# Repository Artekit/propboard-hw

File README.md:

# Artekit PropBoard Hardware

This repository contains hardware-related files for the [Artekit PropBoard](https://www.artekit.eu/products/devboards/propboard/).

## Documentation

* [Product page](https://www.artekit.eu/products/devboards/propboard/)
* [Manual & APIs](https://www.artekit.eu/doc/categories/propboard/)

## License

Released under the Creative Commons Attribution Share-Alike 3.0 License (http://creativecommons.org/licenses/by-sa/3.0)

Copyright (c) 2017 Artekit Labs.

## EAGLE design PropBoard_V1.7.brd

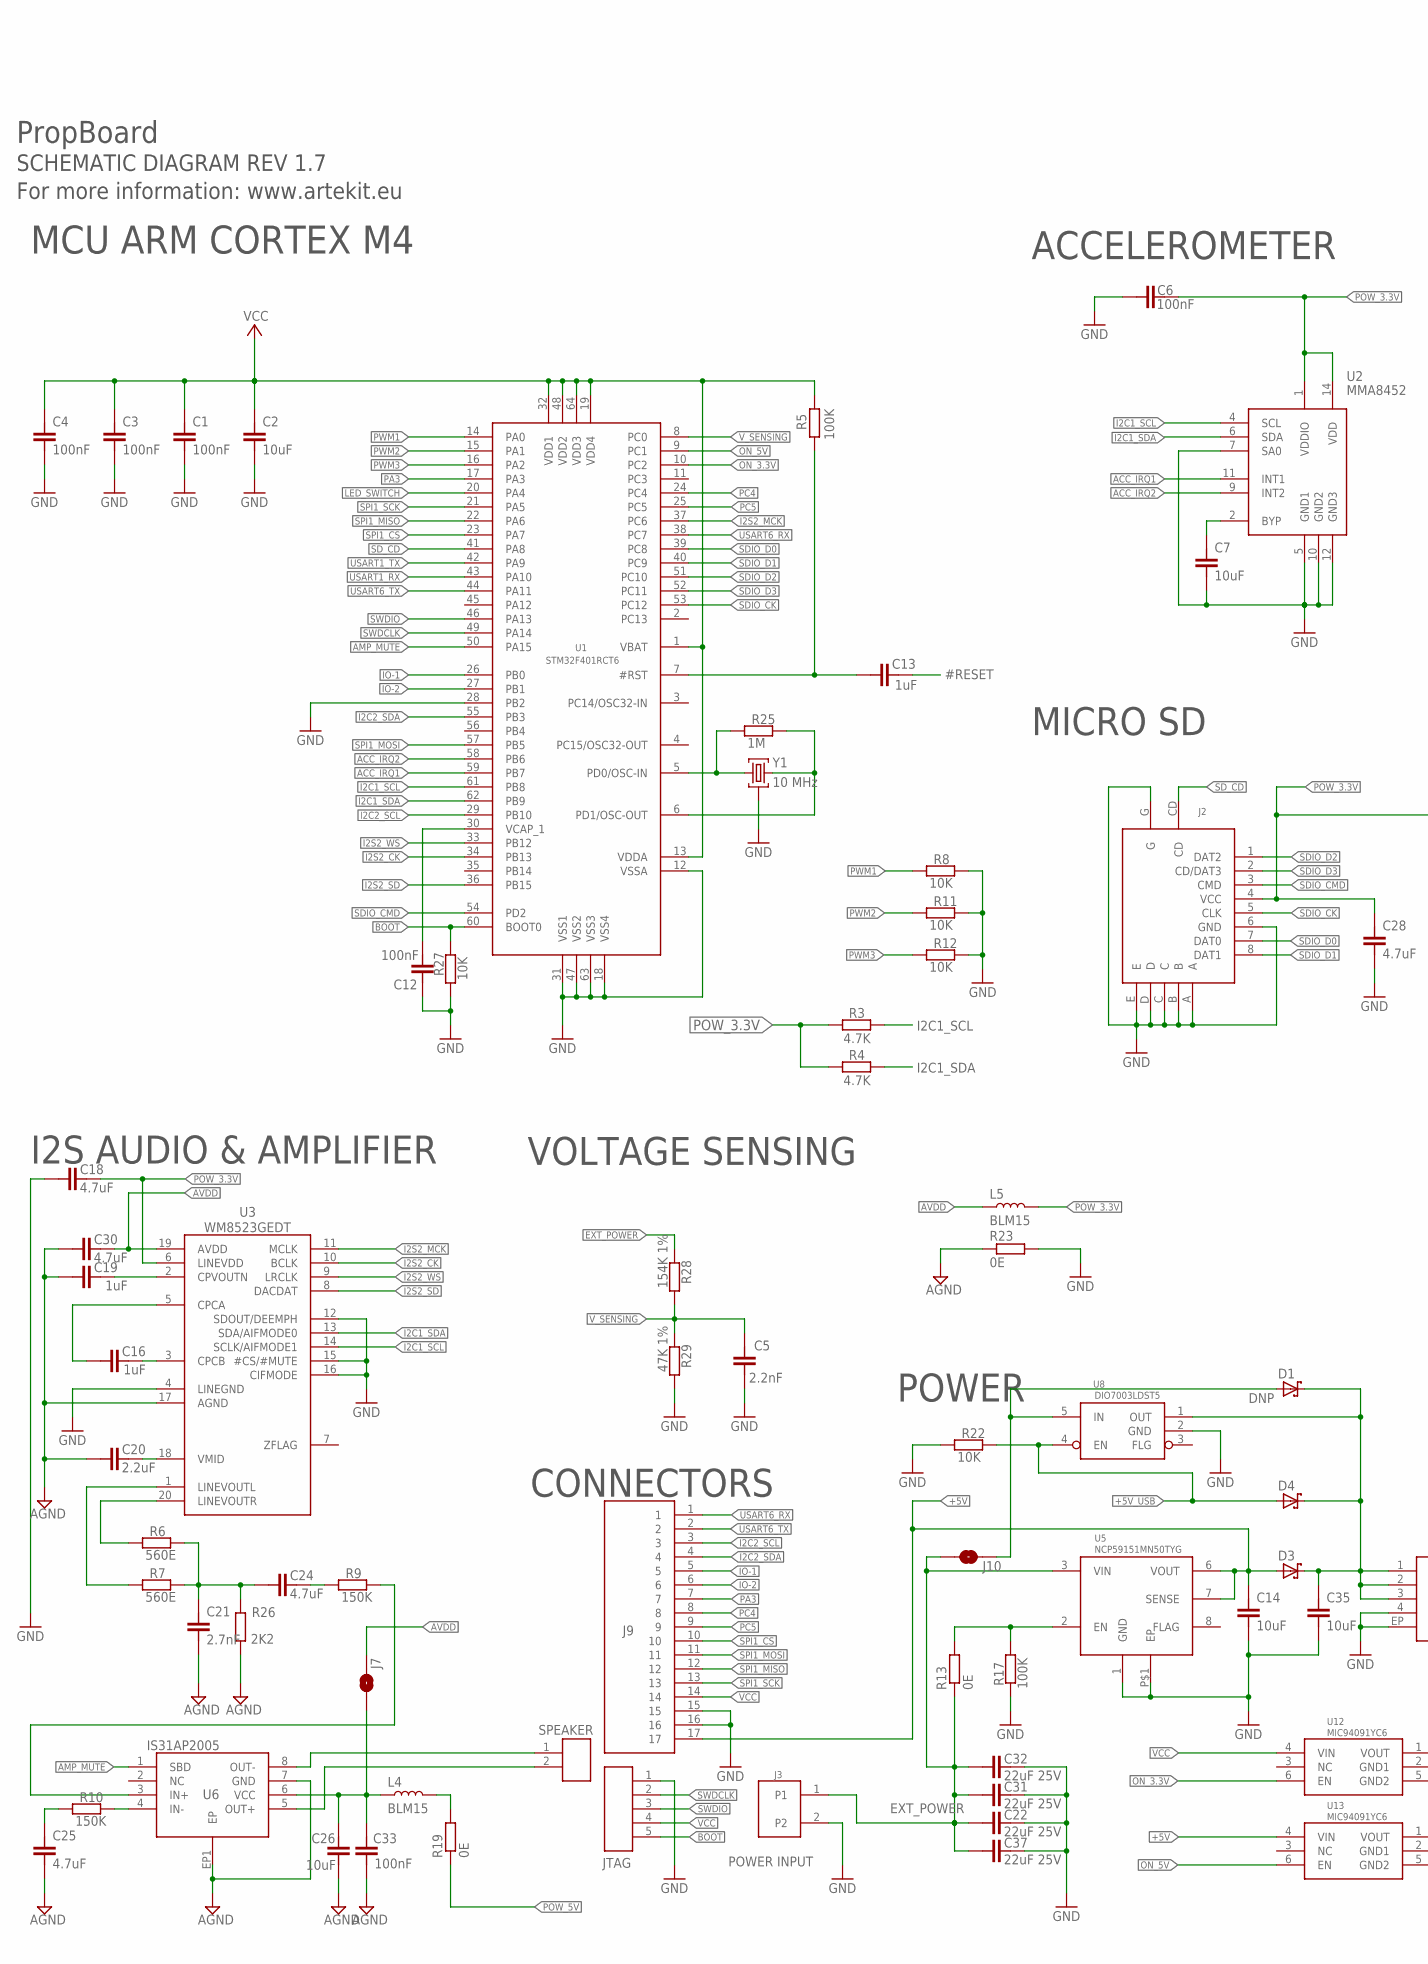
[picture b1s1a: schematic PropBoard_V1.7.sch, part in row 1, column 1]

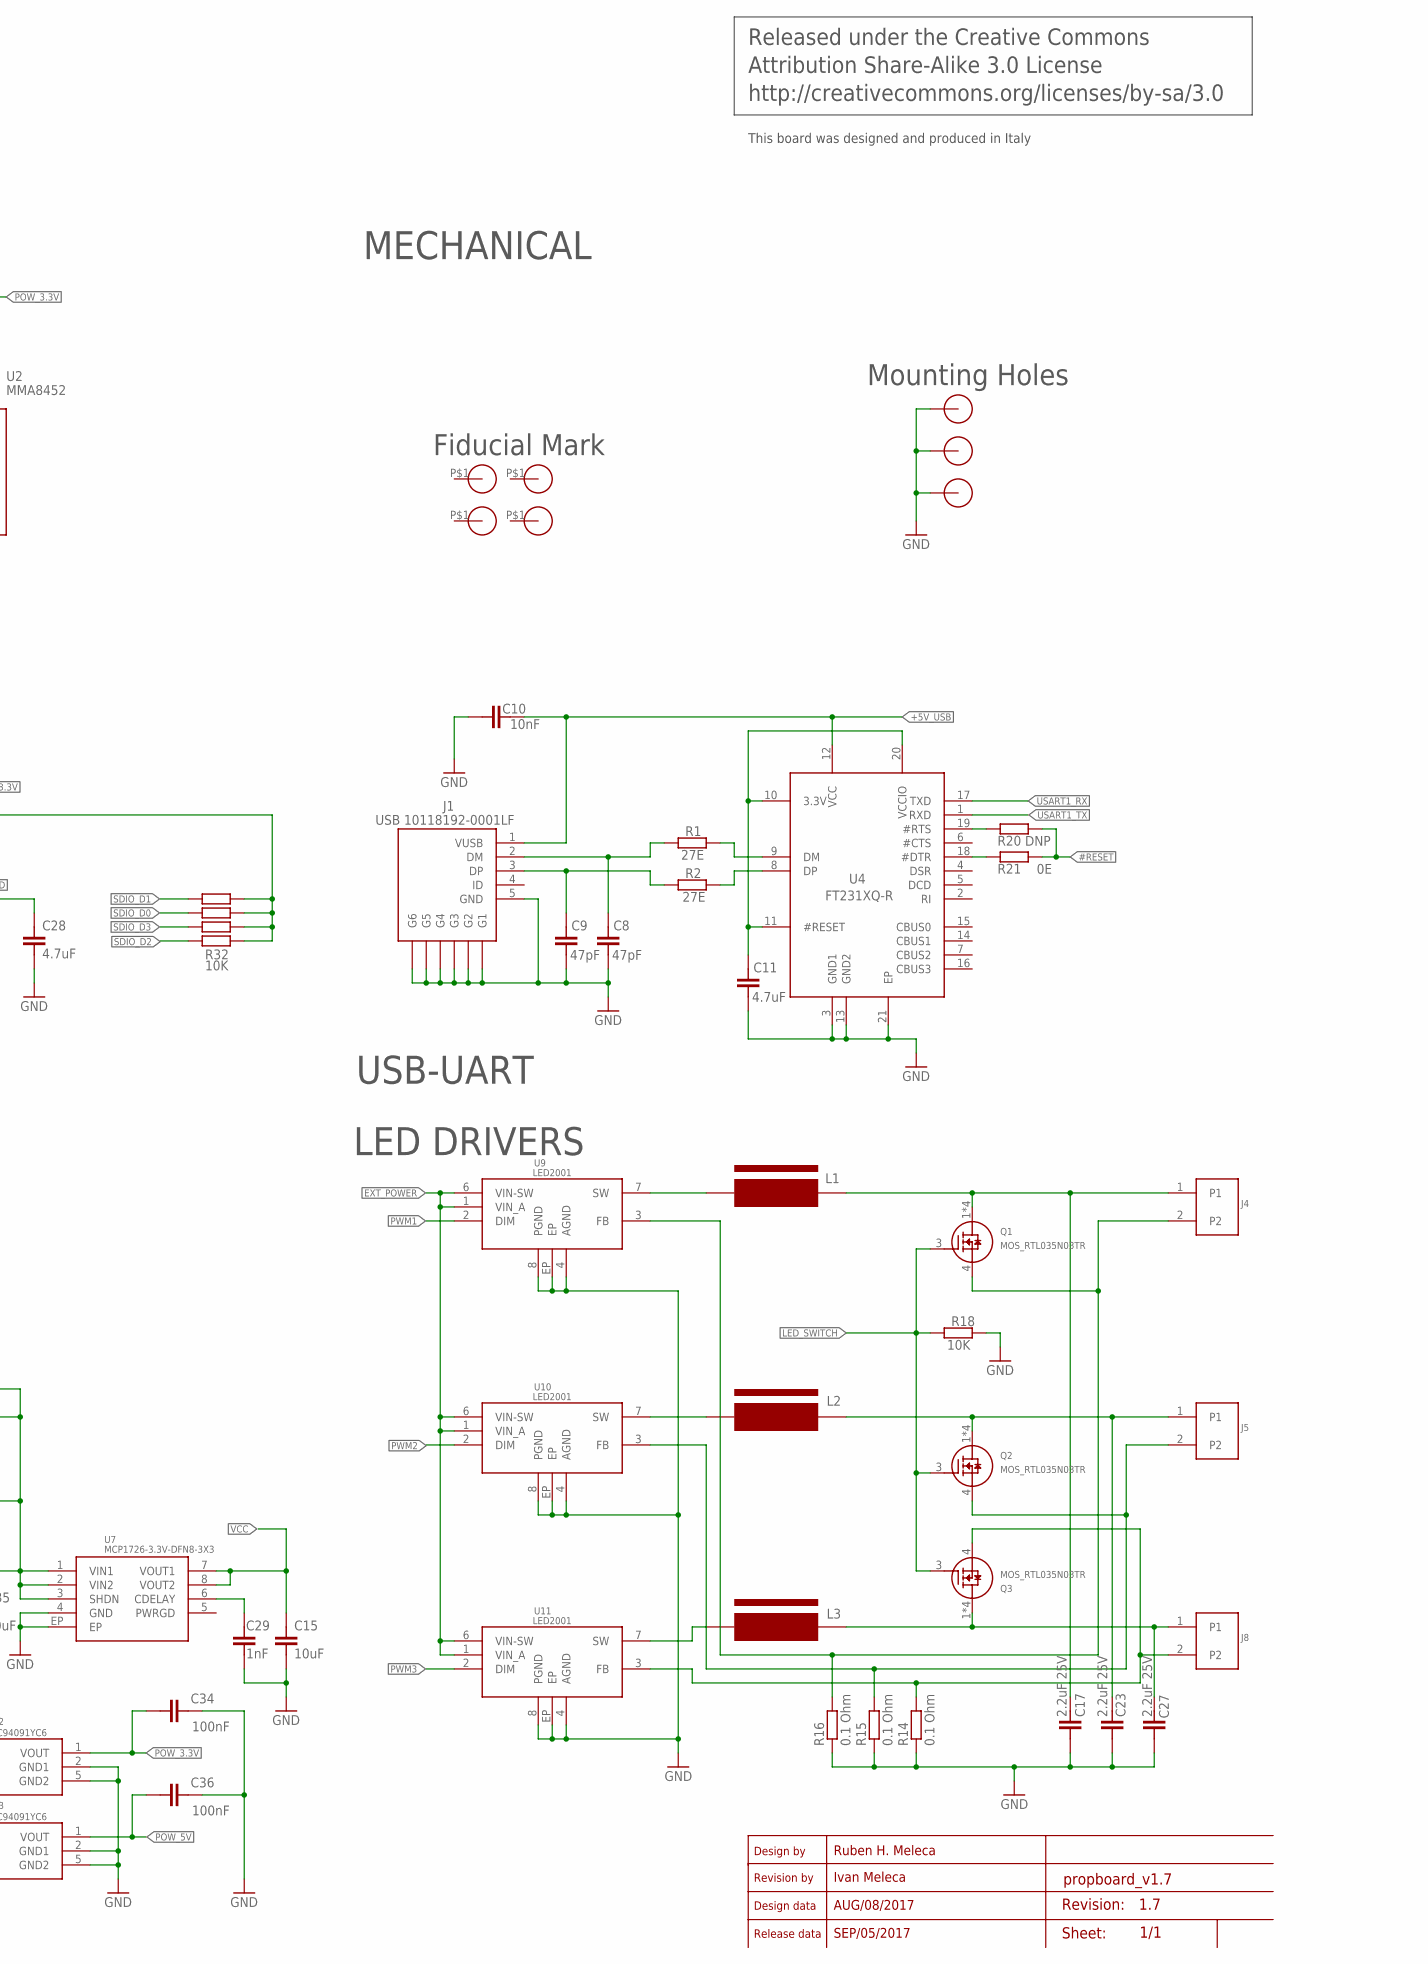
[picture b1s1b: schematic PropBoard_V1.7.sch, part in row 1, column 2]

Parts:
C1, C3, C4, C6, C12, C33, C34, C36: 100nF; C0402
C2, C7, C14, C15, C26, C35: 10uF; C0402
C5: 2.2nF; C0402
C8, C9: 47pF; C0402
C10: 10nF; C0402
C11, C18, C24, C25, C28, C30: 4.7uF; C0402
C13, C19: 1uF; C0402
C16: 1uF; C0402-WIDE
C17, C23, C27: 2.2uF 25V; C0603
C20: 2.2uF; C0402
C21: 2.7nF; C0402
C22, C31, C32, C37: 22uF 25V; C0805
C29: 1nF; C0402
D1: DNP; SOD-323
D3, D4: BAT60; SOD-323
J1: USB 10118192-0001LF; CON-USB-MICRO-B-SMD
J2: MICRO-SD-CON-MOLEX-503182-0852
J3: PROP-POWER-PAD; 2-WAY-POWER-PAD
J4, J5, J8: PROP-LED-PAD; 2-WAY-POWER-PAD-SMALL
J6: CON-PH-1X02-P0.1"2MM; PIN-HEADER-1X02-P2MM
J7, J10: JUMPER-1-OPEN
J9: CON-PH-1X17-P0.1; PIN-HEADER-1X17-NODASH
L1, L2, L3: SRN6028-3R9M; IND-MURATA-DG6050-SERIES; MPN SRN6028-3R9M
L4, L5: BLM15; I0402; MPN BLM15AG102SN1
Q1, Q2, Q3: MOS_RTL035N03TR; SOT-363-6
R1, R2: 27E; R0402
R3, R4: 4.7K; R0402
R5, R17: 100K; R0402
R6, R7: 560E; R0402
R8, R11, R12, R18, R22, R27: 10K; R0402
R9, R10: 150K; R0402
R13, R19: 0E; R0603
R14, R15, R16: 0.1 Ohm; R0805
R20: DNP; R0402
R21: 0E; R0402
R23: 0E; R0402; MPN BLM15AG102SN1
R25: 1M; R0402
R26: 2K2; R0402
R28: 154K 1%; R0402
R29: 47K 1%; R0402
R32: 10K; RES-ARRAY-0603
U1: STM32F401RCT6; LQFP64-10X10-P0.50; MPN STM32F401RCT6
U2: MMA8452; QFN-COL-16-3X3-P0.50-MMA8452
U3: WM8523GEDT; TSSOP-20
U4: FT231XQ-R; QFN20-4X4-P0.50
U5: NCP59151MN50TYG; DFN8-4X4
U6: IS31AP2005; DFN-8-3X3MM-P0.65
U7: MCP1726-3.3V-DFN8-3X3; DFN8-3X3
U8: DIO7003LDST5; SOT23-5
U9, U10, U11: LED2001; VFQFPN-8
U12, U13: MIC94091YC6; SOT363-6
U$1: CON-PH-1X05-P0.1"; PIN-HEADER-1X05-NODASH
U$2, U$3, U$4: HOLE-2MM-METALIZED
U$5, U$6, U$8, U$9: FIDUTIAL_1.2MM
Y1: 10 MHz; RESONATOR-MURATA-CSTCE-SERIES

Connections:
#RESET: C13.2, R20.1, R21.1
+5V: C14.1, D3.A, J9.17, U5.6 (VOUT), U5.7 (SENSE), U13.4 (VIN)
+5V_USB: C10.2, D4.A, J1.1 (VUSB), R22.2, U4.12 (VCC), U8.4 (EN)
ACC_IRQ1: U1.59 (PB7), U2.11 (INT1)
ACC_IRQ2: U1.58 (PB6), U2.9 (INT2)
AGND: C19.1, C20.1, C21.2, C25.2, C26.2, C30.1, C33.2, R23.1, R26.1, U3.17 (AGND), U6.7 (GND), U6.EP1 (EP)
AMP_MUTE: U1.50 (PA15), U6.1 (SBD)
AVDD: C30.2, J7.2, L5.1, U3.19 (AVDD)
BOOT: R27.2, U1.60 (BOOT0), U$1.5
EXT_POWER: C22.1, C31.1, C32.1, C37.1, J3.1, J10.1, R13.1, R28.2, U5.3 (VIN), U9.1 (VIN_A), U9.6 (VIN-SW), U10.1 (VIN_A), U10.6 (VIN-SW), U11.1 (VIN_A), U11.6 (VIN-SW)
GND: C1.2, C2.2, C3.2, C4.2, C5.2, C6.1, C7.2, C8.1, C9.1, C10.1, C11.1, C12.2, C14.2, C15.2, C17.2, C18.1, C22.2, C23.2, C27.2, C28.2, C29.2, C31.2, C32.2, C34.2, C35.2, C36.2, C37.2, J1.5 (GND), J1.6 (G1), J1.7 (G2), J1.8 (G3), J1.9 (G4), J1.10 (G5), J1.11 (G6), J2.6 (GND), J2.A, J2.B, J2.C, J2.D, J2.E, J2.G, J3.2, J9.15, J9.16, R8.2, R11.2, R12.2, R14.1, R15.1, R16.1, R17.2, R18.2, R22.1, R23.2, R27.1, R29.1, U1.12 (VSSA), U1.18 (VSS4), U1.28 (PB2), U1.31 (VSS1), U1.47 (VSS2), U1.63 (VSS3), U2.5 (GND1), U2.7 (SA0), U2.10 (GND2), U2.12 (GND3), U3.4 (LINEGND), U3.12 (SDOUT/DEEMPH), U3.15 (#CS/#MUTE), U3.16 (CIFMODE), U4.3 (GND1), U4.13 (GND2), U4.21 (EP), U5.1 (GND), U5.P$1 (EP), U7.4 (GND), U7.EP, U8.2 (GND), U9.4 (AGND), U9.8 (PGND), U9.EP, U10.4 (AGND), U10.8 (PGND), U10.EP, U11.4 (AGND), U11.8 (PGND), U11.EP, U12.2 (GND1), U12.5 (GND2), U13.2 (GND1), U13.5 (GND2), U$1.1, U$2.1, U$3.1, U$4.1, Y1.2
I2C1_SCL: R3.1, U1.61 (PB8), U2.4 (SCL), U3.14 (SCLK/AIFMODE1)
I2C1_SDA: R4.1, U1.62 (PB9), U2.6 (SDA), U3.13 (SDA/AIFMODE0)
I2C2_SCL: J9.3, U1.29 (PB10)
I2C2_SDA: J9.4, U1.55 (PB3)
I2S2_CK: U1.34 (PB13), U3.10 (BCLK)
I2S2_MCK: U1.37 (PC6), U3.11 (MCLK)
I2S2_SD: U1.36 (PB15), U3.8 (DACDAT)
I2S2_WS: U1.33 (PB12), U3.9 (LRCLK)
IO-1: J9.5, U1.26 (PB0)
IO-2: J9.6, U1.27 (PB1)
LED_SWITCH: Q1.3 (G), Q2.3 (G), Q3.3 (G), R18.1, U1.20 (PA4)
unnamed: R1.2, U4.9 (DM)
unnamed: R2.2, U4.8 (DP)
unnamed: C8.2, J1.2 (DM), R1.1
unnamed: C9.2, J1.3 (DP), R2.1
unnamed: R10.2, U6.4 (IN-)
unnamed: C11.2, U4.10 (3.3V), U4.11 (#RESET), U4.20 (VCCIO)
unnamed: C7.1, U2.2 (BYP)
unnamed: L1.1, U9.7 (SW)
unnamed: C13.1, R5.1, U1.7 (#RST)
unnamed: R25.1, U1.5 (PD0/OSC-IN), Y1.1
unnamed: R25.2, U1.6 (PD1/OSC-OUT), Y1.3
unnamed: C16.2, U3.3 (CPCB)
unnamed: C17.1, J4.1, L1.2, Q1.1 (D), Q1.2 (D), Q1.5 (D), Q1.6 (D)
unnamed: C16.1, U3.5 (CPCA)
unnamed: C19.2, U3.2 (CPVOUTN)
unnamed: J4.2, Q1.4 (S), R16.2, U9.3 (FB)
unnamed: C20.2, U3.18 (VMID)
unnamed: R6.1, U3.20 (LINEVOUTR)
unnamed: R7.1, U3.1 (LINEVOUTL)
unnamed: R20.2, U4.19 (#RTS)
unnamed: C21.1, C24.1, R6.2, R7.2, R26.2
unnamed: R21.2, U4.18 (#DTR)
unnamed: C24.2, R9.1
unnamed: R9.2, U6.3 (IN+)
unnamed: L4.2, R19.2
unnamed: C25.1, R10.1
unnamed: J6.1, U6.8 (OUT-)
unnamed: J8.2, Q3.4 (S), R14.2, U11.3 (FB)
unnamed: C26.1, C33.1, J7.1, L4.1, U6.6 (VCC)
unnamed: J5.2, Q2.4 (S), R15.2, U10.3 (FB)
unnamed: C35.1, D1.C, D3.C, D4.C, U7.1 (VIN1), U7.2 (VIN2), U7.3 (SHDN), U8.1 (OUT)
unnamed: R13.2, R17.1, U5.2 (EN)
unnamed: C23.1, J5.1, L2.2, Q2.1 (D), Q2.2 (D), Q2.5 (D), Q2.6 (D)
unnamed: C27.1, J8.1, L3.2, Q3.1 (D), Q3.2 (D), Q3.5 (D), Q3.6 (D)
unnamed: L2.1, U10.7 (SW)
unnamed: L3.1, U11.7 (SW)
unnamed: J6.2, U6.5 (OUT+)
unnamed: D1.A, J10.2, U8.5 (IN)
unnamed: C29.1, U7.6 (CDELAY)
unnamed: C12.1, U1.30 (VCAP_1)
ON_3.3V: U1.10 (PC2), U12.6 (EN)
ON_5V: U1.9 (PC1), U13.6 (EN)
PA3: J9.7, U1.17 (PA3)
PC4: J9.8, U1.24 (PC4)
PC5: J9.9, U1.25 (PC5)
POW_3.3V: C6.2, C18.2, C28.1, C34.1, J2.4 (VCC), L5.2, R3.2, R4.2, R32.2, R32.4, R32.6, R32.8, U2.1 (VDDIO), U2.14 (VDD), U3.6 (LINEVDD), U12.1 (VOUT)
POW_5V: C36.1, R19.1, U13.1 (VOUT)
PWM1: R8.1, U1.14 (PA0), U9.2 (DIM)
PWM2: R11.1, U1.15 (PA1), U10.2 (DIM)
PWM3: R12.1, U1.16 (PA2), U11.2 (DIM)
SDIO_CK: J2.5 (CLK), U1.53 (PC12)
SDIO_CMD: J2.3 (CMD), U1.54 (PD2)
SDIO_D0: J2.7 (DAT0), R32.3, U1.39 (PC8)
SDIO_D1: J2.8 (DAT1), R32.1, U1.40 (PC9)
SDIO_D2: J2.1 (DAT2), R32.7, U1.51 (PC10)
SDIO_D3: J2.2 (CD/DAT3), R32.5, U1.52 (PC11)
SD_CD: J2.CD, U1.41 (PA8)
SPI1_CS: J9.10, U1.23 (PA7)
SPI1_MISO: J9.12, U1.22 (PA6)
SPI1_MOSI: J9.11, U1.57 (PB5)
SPI1_SCK: J9.13, U1.21 (PA5)
SWDCLK: U1.49 (PA14), U$1.2
SWDIO: U1.46 (PA13), U$1.3
USART1_RX: U1.43 (PA10), U4.17 (TXD)
USART1_TX: U1.42 (PA9), U4.1 (RXD)
USART6_RX: J9.1, U1.38 (PC7)
USART6_TX: J9.2, U1.44 (PA11)
VCC: C1.1, C2.1, C3.1, C4.1, C15.1, J9.14, R5.2, U1.1 (VBAT), U1.13 (VDDA), U1.19 (VDD4), U1.32 (VDD1), U1.48 (VDD2), U1.64 (VDD3), U7.7 (VOUT1), U7.8 (VOUT2), U12.4 (VIN), U$1.4
V_SENSING: C5.1, R28.1, R29.2, U1.8 (PC0)

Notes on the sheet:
POWER INPUT
JTAG
SPEAKER
POWER
CONNECTORS
LED DRIVERS
USB-UART
I2S AUDIO & AMPLIFIER
MCU ARM CORTEX M4
VOLTAGE SENSING
MICRO SD
ACCELEROMETER
MECHANICAL
PropBoard
SCHEMATIC DIAGRAM REV 1.7
For more information: www.artekit.eu
Released under the Creative Commons
Attribution Share-Alike 3.0 License
http://creativecommons.org/licenses/by-sa/3.0
This board was designed and produced in Italy
Fiducial Mark
Mounting Holes
Sheet:
Design by
Revision by
Design data
Release data
Revision:
Ruben H. Meleca
Ivan Meleca
AUG/08/2017
SEP/05/2017
1.7
DNP

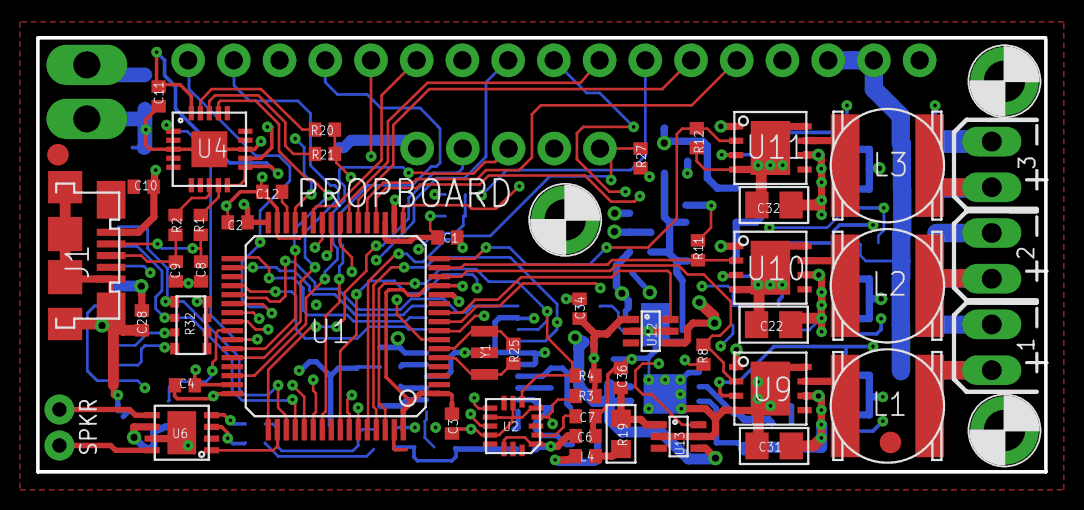
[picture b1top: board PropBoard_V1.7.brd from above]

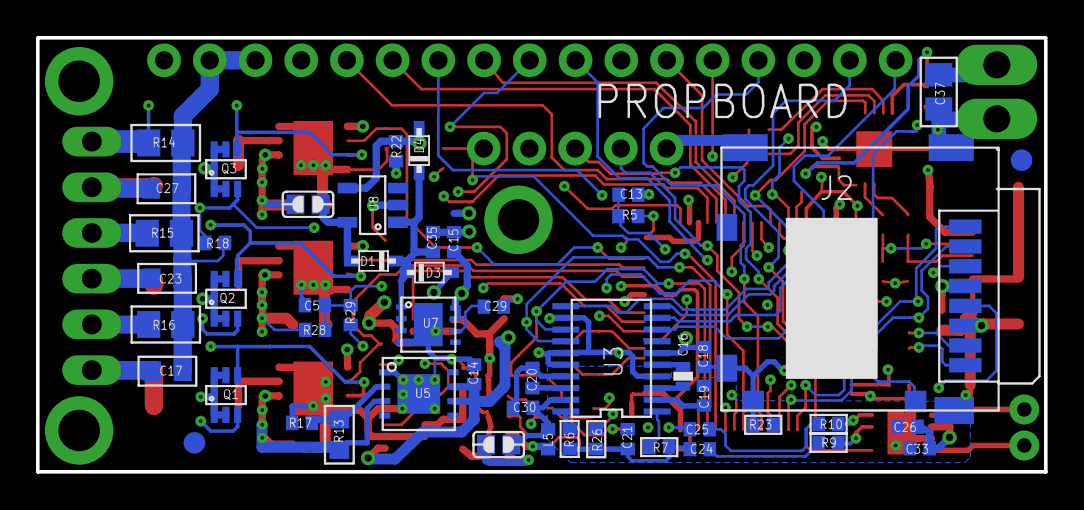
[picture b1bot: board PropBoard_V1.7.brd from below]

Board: 2 copper layers, 56.0 x 24.1 mm, 109 parts (52 on the bottom side), 91 nets.

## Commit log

2017-10-13 :octocat: Added .gitattributes & .gitignore files
2017-10-13 Added README.md
